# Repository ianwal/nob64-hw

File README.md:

# nob64 HW

Separate repository for the hardware used in the nob64 controller PCB.

This is a WIP. Nothing has been tested yet.

## Resources

https://github.com/ncarandini/KiCad-RP-Pico

https://github.com/PhobGCC/PhobGCC-HW

## TODO

- [ ] Notch remapping (firmware)
- [ ] USB-C to N64 support
- [ ] USB-C to USB-A support for PC
  - It only needs one of the signals in the differential pair, use this for port detection

## Attribution

- [PhobGCC HW Button Pads](https://github.com/PhobGCC/PhobGCCv2-HW)
- [Pico STEP 3D model](https://pip.raspberrypi.com/documents/RP-008318-DS)

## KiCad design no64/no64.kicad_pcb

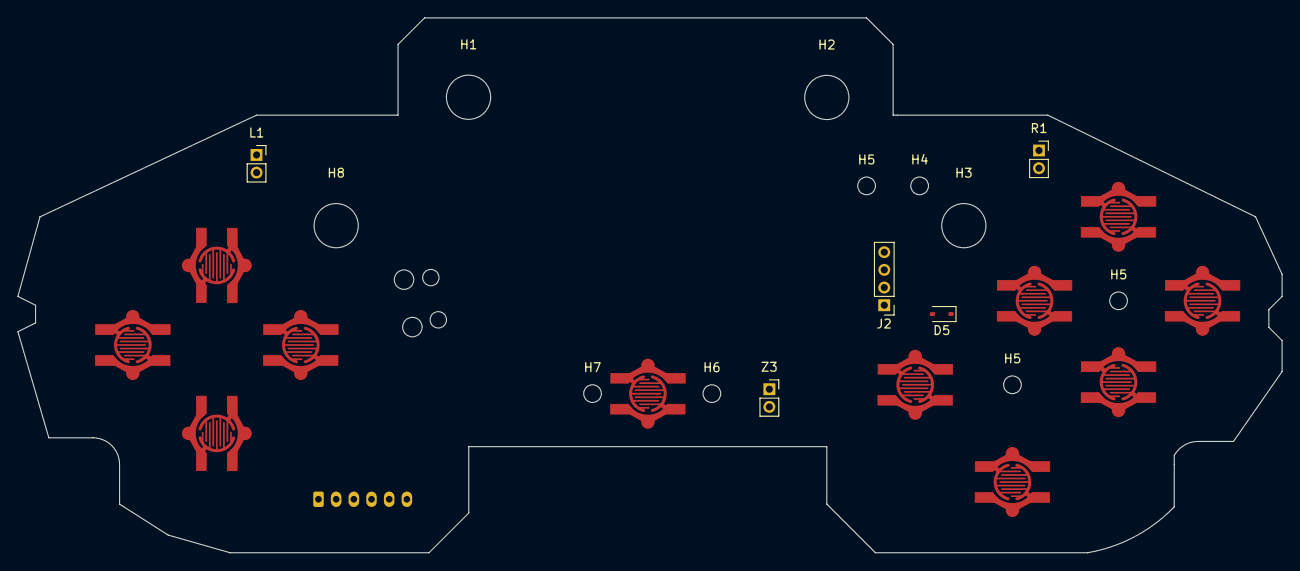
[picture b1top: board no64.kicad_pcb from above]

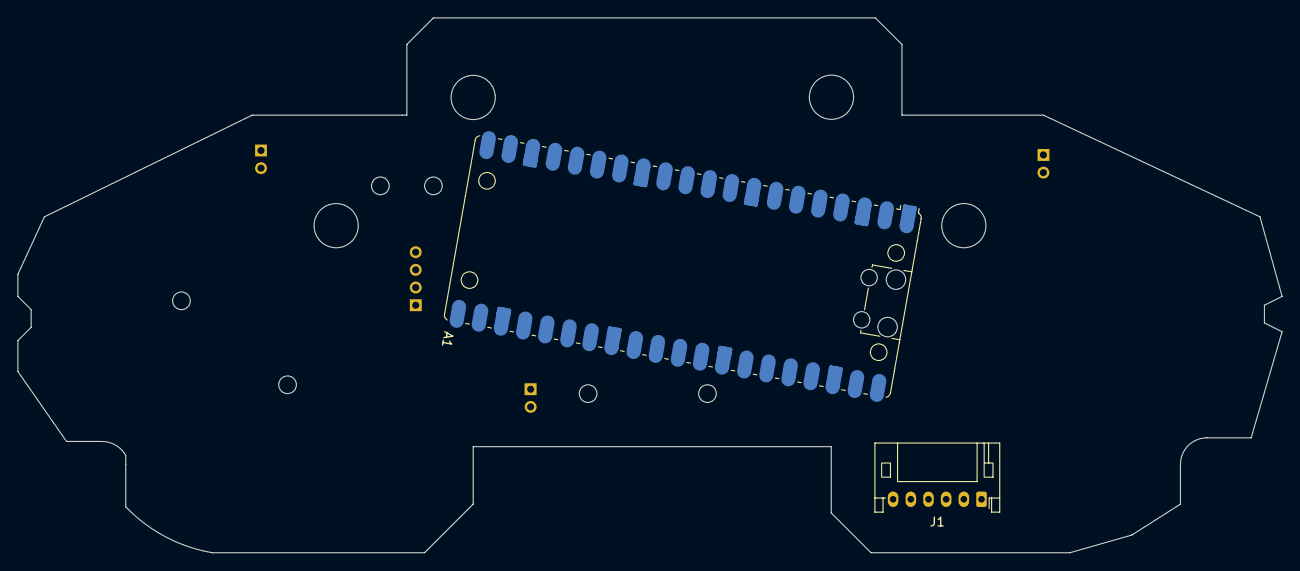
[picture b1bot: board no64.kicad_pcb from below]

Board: 2 copper layers, 143.0 x 60.5 mm, 28 parts (2 on the bottom side), 18 nets, no tracks yet.

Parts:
A1: RaspberryPi_Pico; RaspberryPi_Pico_Common_SMD
D5: CUS10S30,H3F; D_SOD-323
H1, H2, H3, H8: 5.0mm; MountingHole_5mm
H4, H5, H5#2, H5#3, H6, H7: 2.0mm; MountingHole_2mm
J1: Analog Stick; JST_PH_S6B-PH-K_1x06_P2.00mm_Horizontal
J2: Conn_01x04_Socket; PinHeader_1x04_P2.00mm_Vertical
L1: Conn_01x02; PinSocket_1x02_P2.00mm_Vertical
R1: Conn_01x02; PinSocket_1x02_P2.00mm_Vertical
SW2: A; Dpad_Contact_TL3315NF_2_ZigZag
SW3: B; Dpad_Contact_TL3315NF_2_ZigZag
SW4: Dleft; Dpad_Contact_TL3315NF_2_ZigZag
SW5: Dup; Dpad_Contact_TL3315NF_2_ZigZag
SW6: Dright; Dpad_Contact_TL3315NF_2_ZigZag
SW7: Ddown; Dpad_Contact_TL3315NF_2_ZigZag
SW8: START; Dpad_Contact_TL3315NF_2_ZigZag
SW9: Cleft; Dpad_Contact_TL3315NF_2_ZigZag
SW10: Cup; Dpad_Contact_TL3315NF_2_ZigZag
SW11: Cright; Dpad_Contact_TL3315NF_2_ZigZag
SW12: Cdown; Dpad_Contact_TL3315NF_2_ZigZag
Z3: Conn_01x02; PinSocket_1x02_P2.00mm_Vertical

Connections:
/A: A1.15 (GPIO11), SW2.1 (A), SW2.2 (A)
/B: A1.14 (GPIO10), SW3.1 (A), SW3.2 (A)
/Cdown: A1.20 (GPIO15), SW12.1 (A), SW12.2 (A)
/Cleft: A1.16 (GPIO12), SW9.1 (A), SW9.2 (A)
/Cright: A1.19 (GPIO14), SW11.1 (A), SW11.2 (A)
/Cup: A1.17 (GPIO13), SW10.1 (A), SW10.2 (A)
/Ddown: SW7.1 (A), SW7.2 (A)
/Dleft: SW4.1 (A), SW4.2 (A)
/Dright: SW6.1 (A), SW6.2 (A)
/Dup: SW5.1 (A), SW5.2 (A)
/JOY_XA: A1.4 (GPIO2), J1.1
/JOY_XB: A1.5 (GPIO3), J1.4
/JOY_YA: A1.6 (GPIO4), J1.6
/JOY_YB: A1.7 (GPIO5), J1.5
/N64 +3V3: D5.2 (A), J2.4
/START: A1.12 (GPIO9), SW8.1 (A), SW8.2 (A)
GND: A1.3 (GND), A1.8 (GND), A1.13 (GND), A1.18 (GND), A1.23 (GND), A1.28 (GND), A1.38 (GND), J1.3, J2.2, L1.1, R1.1, Z3.1
unnamed: A1.39 (VSYS), D5.1 (K)

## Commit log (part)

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2025-12-14 Init
2025-12-14 Add WIP schematic
2025-12-15 WIP add buttons
